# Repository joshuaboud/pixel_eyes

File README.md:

# pixel_eyes
WS2812S Pixel Eyes

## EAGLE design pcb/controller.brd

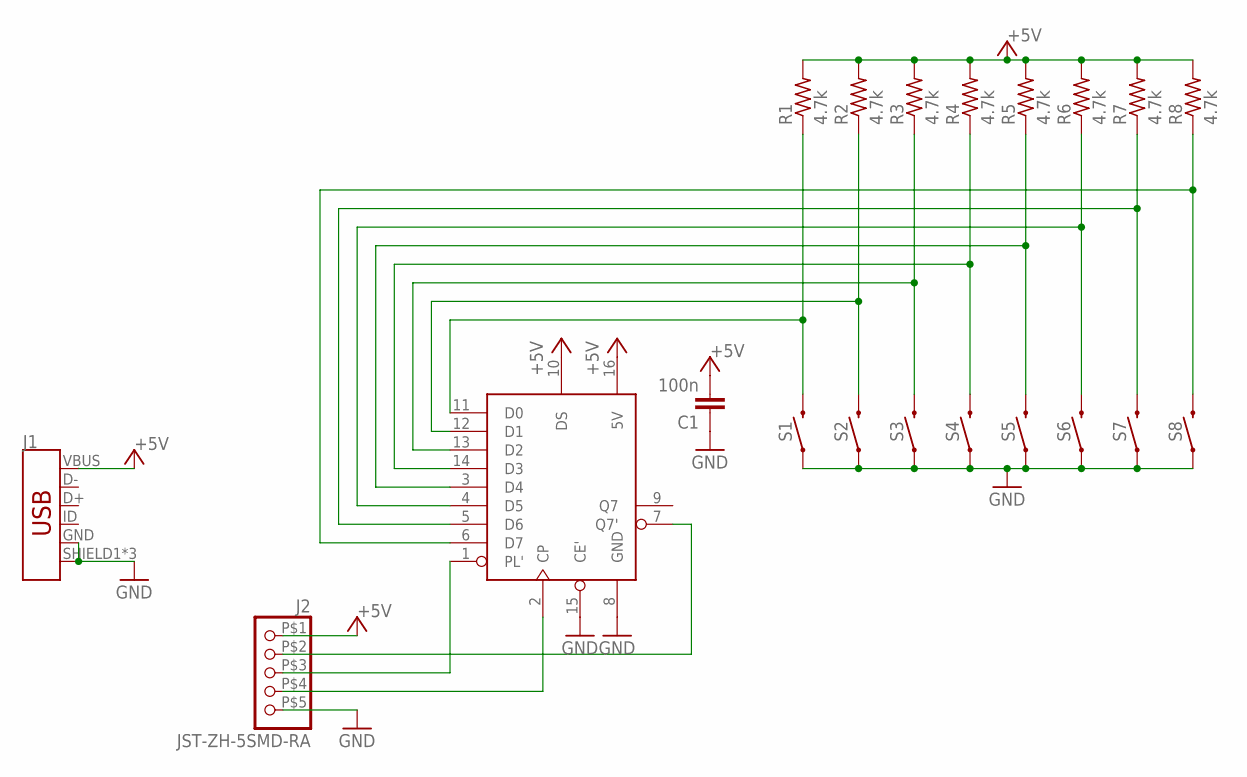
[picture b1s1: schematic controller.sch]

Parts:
C1: 100n; C0603
J1: USB_MICRO-B_FEMALE-SMT; USB-B-MICRO-SMD
J2: JST-ZH-5SMD-RA; JST-ZH-5-SMD-RA
R1, R2, R3, R4, R5, R6, R7, R8: 4.7k; R0603
S1, S2, S3, S4, S5, S6, S7, S8: MOMENTARY-SWITCH-SPST-SMD-6.0X3.5MM; TACTILE_SWITCH_SMD_6.0X3.5MM
U1: 74HCT165TSSOP16; SOP65P640X110-16N

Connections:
+5V: C1.2, J1.VBUS, J2.P$1 (1), R1.2, R2.2, R3.2, R4.2, R5.2, R6.2, R7.2, R8.2, U1.10 (DS), U1.16 (5V)
GND: C1.1, J1.GND, J1.SHIELD1 (SHIELD), J1.SHIELD2 (SHIELD), J1.SHIELD3 (SHIELD), J2.P$5 (5), S1.1, S2.1, S3.1, S4.1, S5.1, S6.1, S7.1, S8.1, U1.8 (GND), U1.15 (CE')
unnamed: J2.P$4 (4), U1.2 (CP)
unnamed: J2.P$3 (3), U1.1 (PL')
unnamed: J2.P$2 (2), U1.7 (Q7')
unnamed: R1.1, S1.2, U1.11 (D0)
unnamed: R2.1, S2.2, U1.12 (D1)
unnamed: R3.1, S3.2, U1.13 (D2)
unnamed: R4.1, S4.2, U1.14 (D3)
unnamed: R5.1, S5.2, U1.3 (D4)
unnamed: R6.1, S6.2, U1.4 (D5)
unnamed: R7.1, S7.2, U1.5 (D6)
unnamed: R8.1, S8.2, U1.6 (D7)

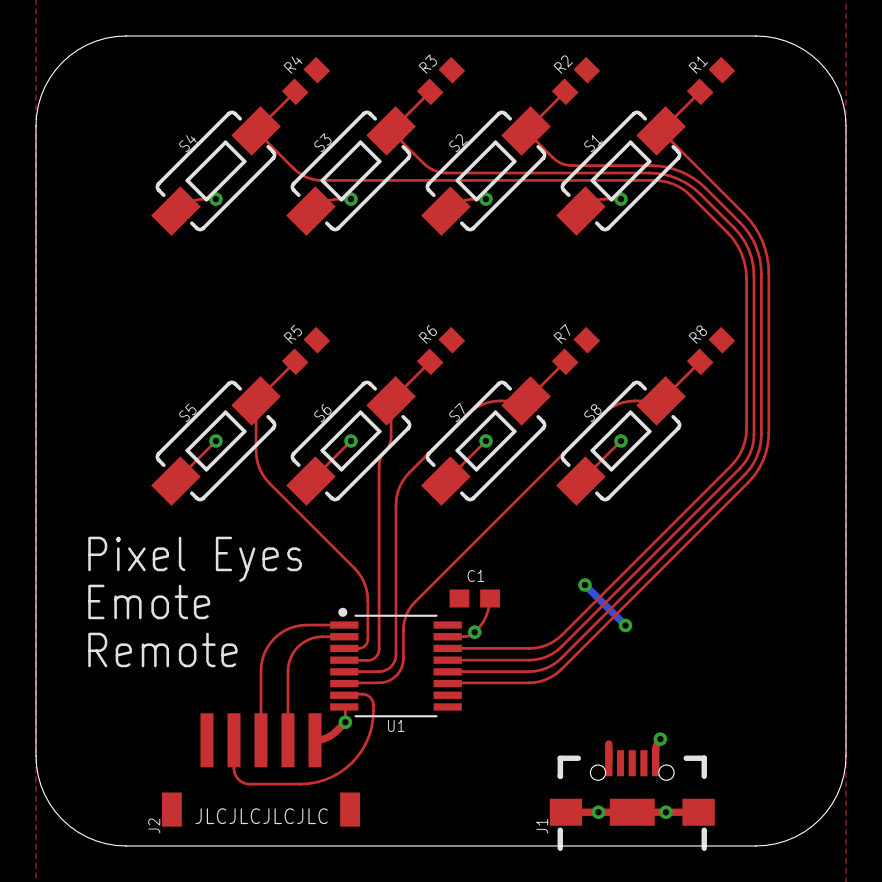
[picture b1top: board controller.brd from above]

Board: 2 copper layers, 45.0 x 45.0 mm, 22 parts (2 on the bottom side), 13 nets.

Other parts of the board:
U$1: SIGNATURE
U$3: LOGO_SILKSCREEN

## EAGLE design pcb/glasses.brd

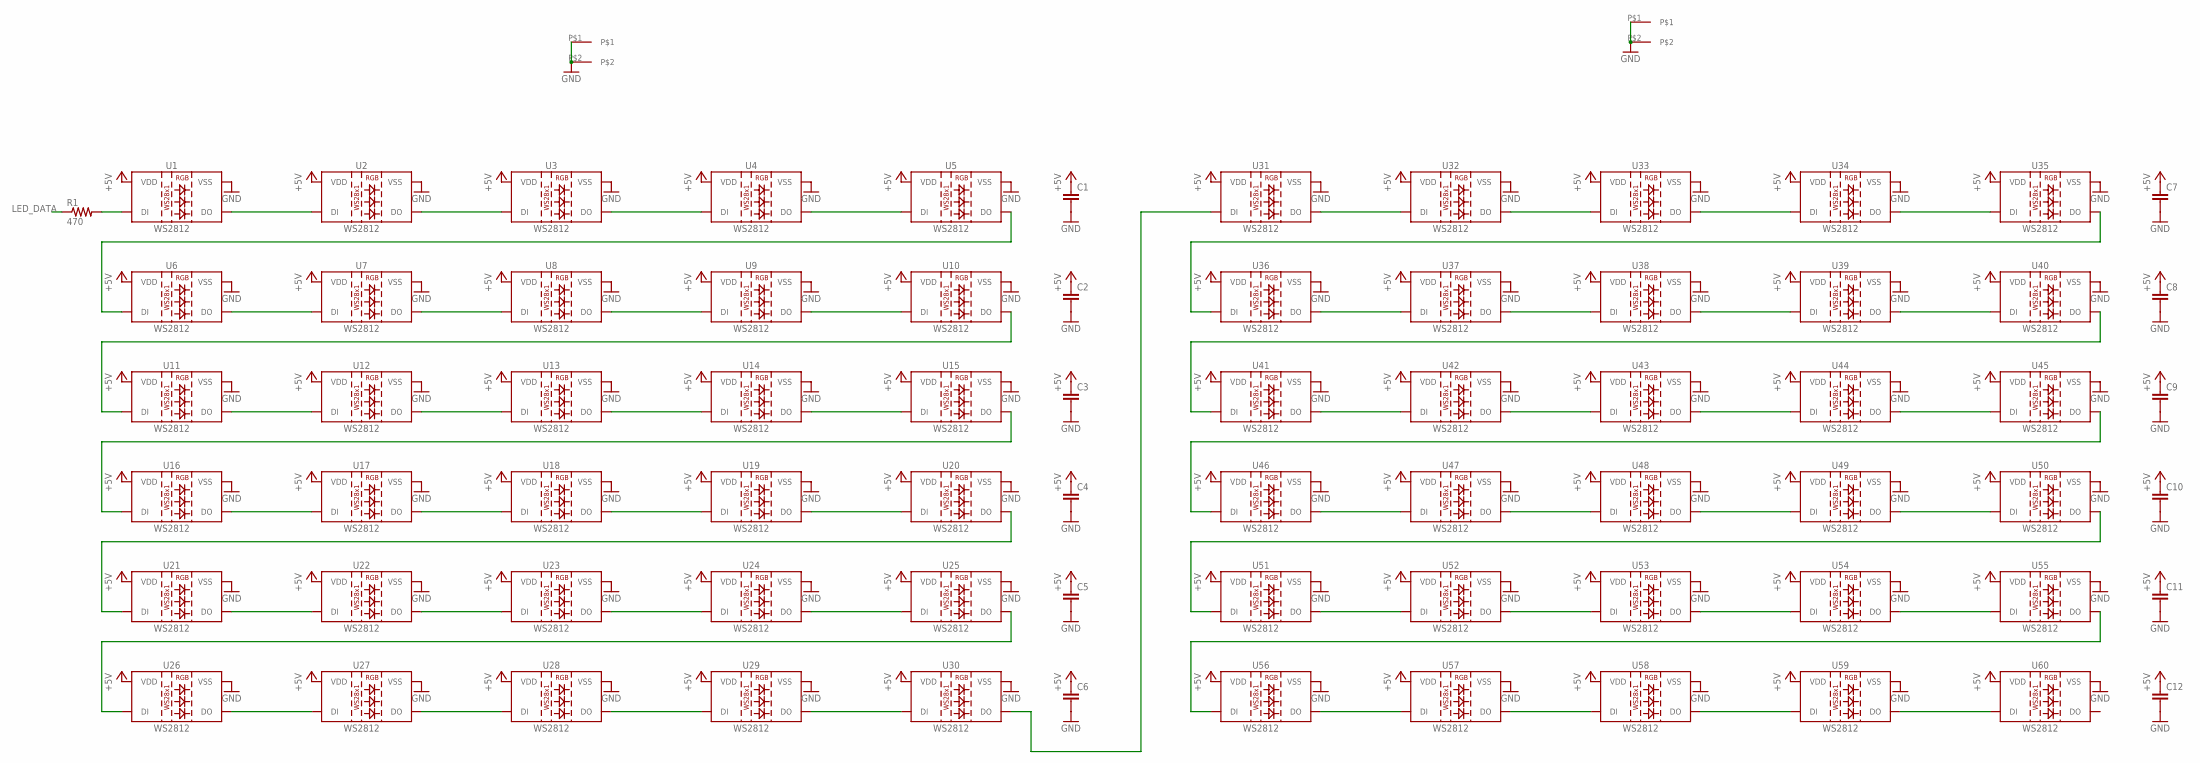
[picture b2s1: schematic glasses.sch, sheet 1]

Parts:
C1, C2, C3, C4, C5, C6, C7, C8, C9, C10, C11, C12: C-EUC0603; C0603
R1: 470; R0603
U1, U2, U3, U4, U5, U6, U7, U8, U9, U10, U11, U12, U13, U14, U15, U16, U17, U18, U19, U20, U21, U22, U23, U24, U25, U26, U27, U28, U29, U30, U31, U32, U33, U34, U35, U36, U37, U38, U39, U40, U41, U42, U43, U44, U45, U46, U47, U48, U49, U50, U51, U52, U53, U54, U55, U56, U57, U58, U59, U60: WS2812; LED-TRICOLOR-5050-IC
U$4, U$5: GLASSES_HINGE

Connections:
+5V: C1.1, C2.1, C3.1, C4.1, C5.1, C6.1, C7.1, C8.1, C9.1, C10.1, C11.1, C12.1, U1.3 (VDD), U1.5 (VDD), U2.3 (VDD), U2.5 (VDD), U3.3 (VDD), U3.5 (VDD), U4.3 (VDD), U4.5 (VDD), U5.3 (VDD), U5.5 (VDD), U6.3 (VDD), U6.5 (VDD), U7.3 (VDD), U7.5 (VDD), U8.3 (VDD), U8.5 (VDD), U9.3 (VDD), U9.5 (VDD), U10.3 (VDD), U10.5 (VDD), U11.3 (VDD), U11.5 (VDD), U12.3 (VDD), U12.5 (VDD), U13.3 (VDD), U13.5 (VDD), U14.3 (VDD), U14.5 (VDD), U15.3 (VDD), U15.5 (VDD), U16.3 (VDD), U16.5 (VDD), U17.3 (VDD), U17.5 (VDD), U18.3 (VDD), U18.5 (VDD), U19.3 (VDD), U19.5 (VDD), U20.3 (VDD), U20.5 (VDD), U21.3 (VDD), U21.5 (VDD), U22.3 (VDD), U22.5 (VDD), U23.3 (VDD), U23.5 (VDD), U24.3 (VDD), U24.5 (VDD), U25.3 (VDD), U25.5 (VDD), U26.3 (VDD), U26.5 (VDD), U27.3 (VDD), U27.5 (VDD), U28.3 (VDD), U28.5 (VDD), U29.3 (VDD), U29.5 (VDD), U30.3 (VDD), U30.5 (VDD), U31.3 (VDD), U31.5 (VDD), U32.3 (VDD), U32.5 (VDD), U33.3 (VDD), U33.5 (VDD), U34.3 (VDD), U34.5 (VDD), U35.3 (VDD), U35.5 (VDD), U36.3 (VDD), U36.5 (VDD), U37.3 (VDD), U37.5 (VDD), U38.3 (VDD), U38.5 (VDD), U39.3 (VDD), U39.5 (VDD), U40.3 (VDD), U40.5 (VDD), U41.3 (VDD), U41.5 (VDD), U42.3 (VDD), U42.5 (VDD), U43.3 (VDD), U43.5 (VDD), U44.3 (VDD), U44.5 (VDD), U45.3 (VDD), U45.5 (VDD), U46.3 (VDD), U46.5 (VDD), U47.3 (VDD), U47.5 (VDD), U48.3 (VDD), U48.5 (VDD), U49.3 (VDD), U49.5 (VDD), U50.3 (VDD), U50.5 (VDD), U51.3 (VDD), U51.5 (VDD), U52.3 (VDD), U52.5 (VDD), U53.3 (VDD), U53.5 (VDD), U54.3 (VDD), U54.5 (VDD), U55.3 (VDD), U55.5 (VDD), U56.3 (VDD), U56.5 (VDD), U57.3 (VDD), U57.5 (VDD), U58.3 (VDD), U58.5 (VDD), U59.3 (VDD), U59.5 (VDD), U60.3 (VDD), U60.5 (VDD); also elsewhere on the board
GND: C1.2, C2.2, C3.2, C4.2, C5.2, C6.2, C7.2, C8.2, C9.2, C10.2, C11.2, C12.2, U1.6 (VSS), U2.6 (VSS), U3.6 (VSS), U4.6 (VSS), U5.6 (VSS), U6.6 (VSS), U7.6 (VSS), U8.6 (VSS), U9.6 (VSS), U10.6 (VSS), U11.6 (VSS), U12.6 (VSS), U13.6 (VSS), U14.6 (VSS), U15.6 (VSS), U16.6 (VSS), U17.6 (VSS), U18.6 (VSS), U19.6 (VSS), U20.6 (VSS), U21.6 (VSS), U22.6 (VSS), U23.6 (VSS), U24.6 (VSS), U25.6 (VSS), U26.6 (VSS), U27.6 (VSS), U28.6 (VSS), U29.6 (VSS), U30.6 (VSS), U31.6 (VSS), U32.6 (VSS), U33.6 (VSS), U34.6 (VSS), U35.6 (VSS), U36.6 (VSS), U37.6 (VSS), U38.6 (VSS), U39.6 (VSS), U40.6 (VSS), U41.6 (VSS), U42.6 (VSS), U43.6 (VSS), U44.6 (VSS), U45.6 (VSS), U46.6 (VSS), U47.6 (VSS), U48.6 (VSS), U49.6 (VSS), U50.6 (VSS), U51.6 (VSS), U52.6 (VSS), U53.6 (VSS), U54.6 (VSS), U55.6 (VSS), U56.6 (VSS), U57.6 (VSS), U58.6 (VSS), U59.6 (VSS), U60.6 (VSS), U$4.P$1, U$4.P$2, U$5.P$1, U$5.P$2; also elsewhere on the board
LED_DATA: R1.1; also elsewhere on the board
unnamed: U1.1 (DO), U2.2 (DI)
unnamed: U2.1 (DO), U3.2 (DI)
unnamed: U3.1 (DO), U4.2 (DI)
unnamed: U4.1 (DO), U5.2 (DI)
unnamed: U5.1 (DO), U6.2 (DI)
unnamed: U6.1 (DO), U7.2 (DI)
unnamed: U7.1 (DO), U8.2 (DI)
unnamed: U8.1 (DO), U9.2 (DI)
unnamed: U9.1 (DO), U10.2 (DI)
unnamed: U10.1 (DO), U11.2 (DI)
unnamed: U11.1 (DO), U12.2 (DI)
unnamed: U12.1 (DO), U13.2 (DI)
unnamed: U13.1 (DO), U14.2 (DI)
unnamed: U14.1 (DO), U15.2 (DI)
unnamed: U15.1 (DO), U16.2 (DI)
unnamed: U16.1 (DO), U17.2 (DI)
unnamed: U17.1 (DO), U18.2 (DI)
unnamed: U18.1 (DO), U19.2 (DI)
unnamed: U19.1 (DO), U20.2 (DI)
unnamed: U20.1 (DO), U21.2 (DI)
unnamed: U21.1 (DO), U22.2 (DI)
unnamed: U22.1 (DO), U23.2 (DI)
unnamed: U23.1 (DO), U24.2 (DI)
unnamed: U24.1 (DO), U25.2 (DI)
unnamed: U25.1 (DO), U26.2 (DI)
unnamed: U26.1 (DO), U27.2 (DI)
unnamed: U27.1 (DO), U28.2 (DI)
unnamed: U28.1 (DO), U29.2 (DI)
unnamed: U29.1 (DO), U30.2 (DI)
unnamed: U31.1 (DO), U32.2 (DI)
unnamed: U32.1 (DO), U33.2 (DI)
unnamed: U33.1 (DO), U34.2 (DI)
unnamed: U34.1 (DO), U35.2 (DI)
unnamed: U35.1 (DO), U36.2 (DI)
unnamed: U36.1 (DO), U37.2 (DI)
unnamed: U37.1 (DO), U38.2 (DI)
unnamed: U38.1 (DO), U39.2 (DI)
unnamed: U39.1 (DO), U40.2 (DI)
unnamed: U40.1 (DO), U41.2 (DI)
unnamed: U41.1 (DO), U42.2 (DI)
unnamed: U42.1 (DO), U43.2 (DI)
unnamed: U43.1 (DO), U44.2 (DI)
unnamed: U44.1 (DO), U45.2 (DI)
unnamed: U45.1 (DO), U46.2 (DI)
unnamed: U46.1 (DO), U47.2 (DI)
unnamed: U47.1 (DO), U48.2 (DI)
unnamed: U48.1 (DO), U49.2 (DI)
unnamed: U49.1 (DO), U50.2 (DI)
unnamed: U50.1 (DO), U51.2 (DI)
unnamed: U51.1 (DO), U52.2 (DI)
unnamed: U52.1 (DO), U53.2 (DI)
unnamed: U53.1 (DO), U54.2 (DI)
unnamed: U54.1 (DO), U55.2 (DI)
unnamed: U55.1 (DO), U56.2 (DI)
unnamed: U56.1 (DO), U57.2 (DI)
unnamed: U57.1 (DO), U58.2 (DI)
unnamed: U58.1 (DO), U59.2 (DI)
unnamed: U59.1 (DO), U60.2 (DI)
unnamed: U30.1 (DO), U31.2 (DI)
unnamed: R1.2, U1.2 (DI)

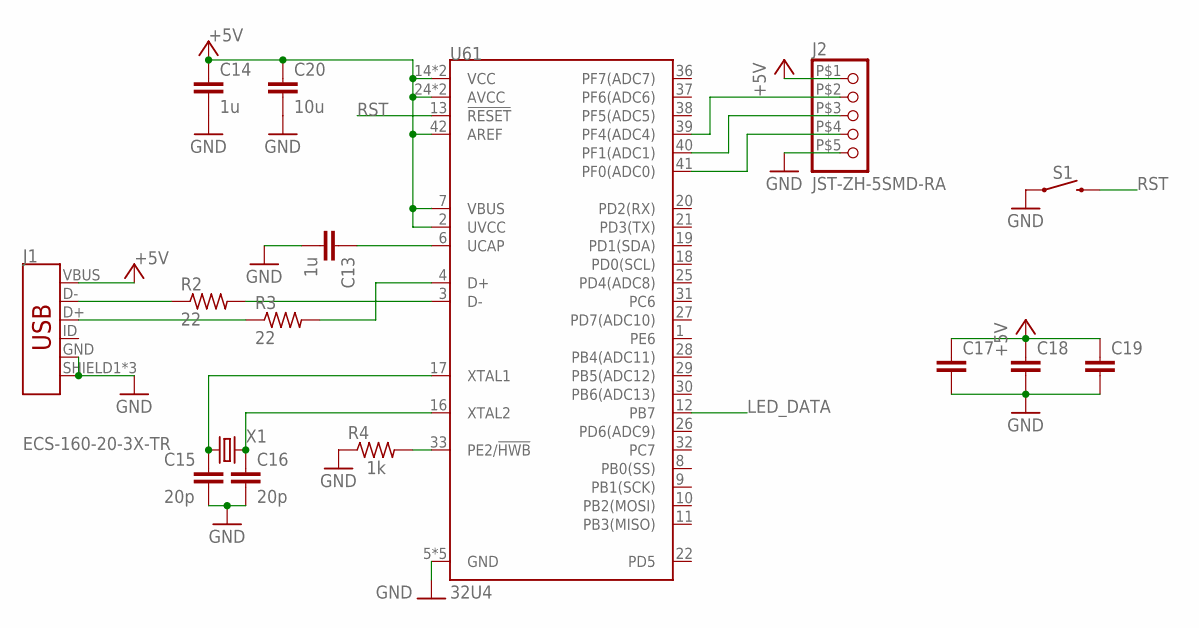
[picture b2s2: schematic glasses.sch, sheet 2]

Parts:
C13, C14: 1u; C0603
C15, C16: 20p; C0603
C17, C18, C19: C-EUC0603; C0603
C20: 10u; C0603
J1: USB_MICRO-B_FEMALE-SMT; USB-B-MICRO-SMD
J2: JST-ZH-5SMD-RA; JST-ZH-5-SMD-RA
R2, R3: 22; R0603
R4: 1k; R0603
S1: MOMENTARY-SWITCH-SPST-SMD-6.0X3.5MM; TACTILE_SWITCH_SMD_6.0X3.5MM
U61: 32U4; QFN-44
X1: ECS-160-20-3X-TR; CRYSTAL-SMD-5X3.2-2PAD

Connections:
+5V: C14.1, C17.1, C18.1, C19.1, C20.1, J1.VBUS, J2.P$1 (1), U61.2 (UVCC), U61.7 (VBUS), U61.14 (VCC), U61.24 (AVCC), U61.34 (VCC), U61.42 (AREF), U61.44 (AVCC); also elsewhere on the board
GND: C13.2, C14.2, C15.2, C16.2, C17.2, C18.2, C19.2, C20.2, J1.GND, J1.SHIELD1 (SHIELD), J1.SHIELD2 (SHIELD), J1.SHIELD3 (SHIELD), J2.P$5 (5), R4.1, S1.1, U61.5 (GND), U61.15 (GND), U61.23 (GND), U61.35 (GND), U61.43 (GND); also elsewhere on the board
LED_DATA: U61.12 (PB7); also elsewhere on the board
unnamed: J2.P$4 (4), U61.41 (PF0(ADC0))
unnamed: C13.1, U61.6 (UCAP)
unnamed: J2.P$3 (3), U61.40 (PF1(ADC1))
unnamed: J2.P$2 (2), U61.39 (PF4(ADC4))
unnamed: C16.1, U61.16 (XTAL2), X1.P$2 (2)
unnamed: C15.1, U61.17 (XTAL1), X1.P$1 (1)
unnamed: R4.2, U61.33 (PE2/!HWB)
RST: S1.2, U61.13 (!RESET)
USB1_N: J1.D-, R2.1
USB1_P: J1.D+, R3.1
USB_N: R2.2, U61.3 (D-)
USB_P: R3.2, U61.4 (D+)

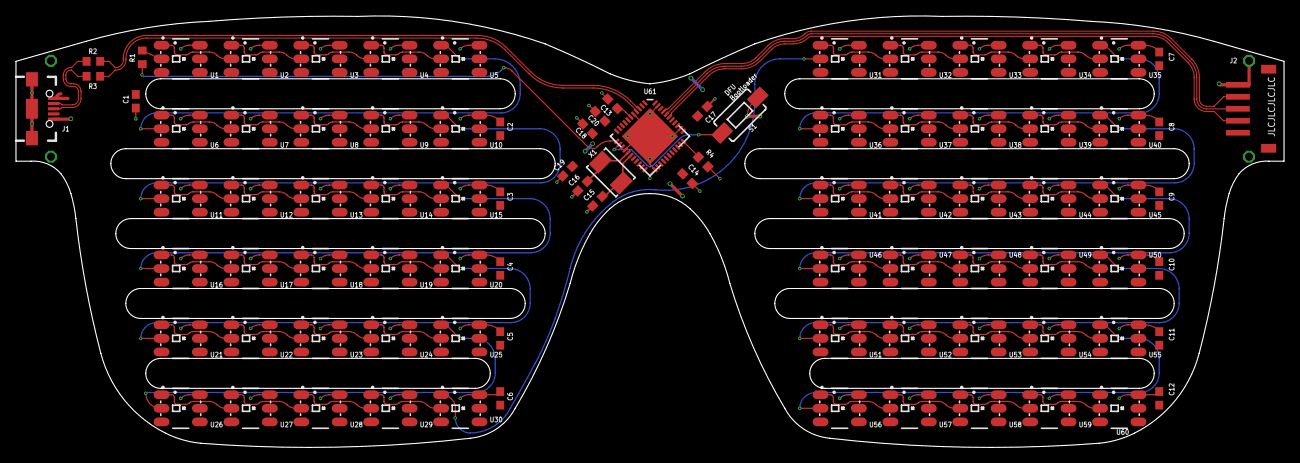
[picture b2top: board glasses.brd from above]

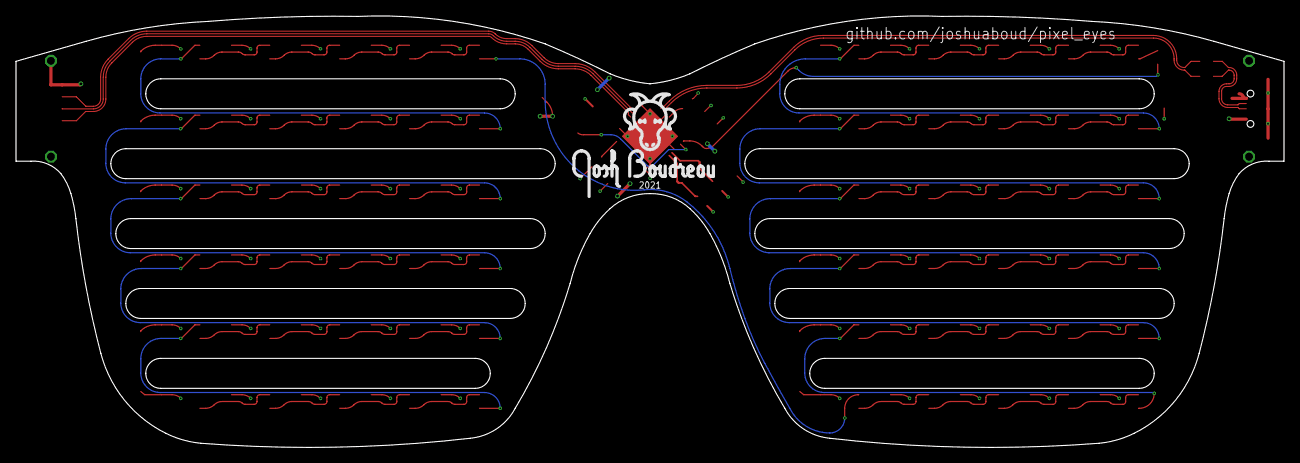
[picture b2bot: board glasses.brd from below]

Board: 2 copper layers, 158.8 x 54.0 mm, 93 parts (2 on the bottom side), 75 nets.

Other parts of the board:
U$1: SIGNATURE
U$2: LOGO_SILKSCREEN

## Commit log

2021-08-13 start route data lines
2021-08-13 finish wiring
2021-08-13 change connector to TE AMP 171826-3
2021-08-13 add library
2021-08-16 start controller design
2021-08-16 change to non-arduino atmega32u4
2021-08-16 start source
2021-08-17 ignore ccls cache
2021-08-17 add License.txt for WS2812 lib
2021-08-17 add build and dist
2021-08-17 ignore vscode settings
2021-08-17 set up makefile
2021-08-17 finish makefile
2021-08-17 change from c11 to gnu11 standard
2021-08-17 work on source
2021-08-18 create Frame struct
2021-08-18 add emote lut
2021-08-19 add simulation
2021-08-19 change RGB6 to be union of bf and uint8_t
2021-08-19 bug fixes
2021-08-19 remove LED number output
2021-08-19 finish simulation env
2021-08-20 add program to draw emotes
2021-08-20 implement saving frames to .c file
2021-08-24 implement saving, loading, frame insert/delete
2021-08-24 add changing duration
2021-08-24 append frame to end
2021-08-24 add edit frames target
2021-08-24 add default blink animation
2021-08-30 add previewing frames
2021-08-30 save frames
2021-09-05 make full glasses and add mcu to them
2021-09-06 finish up glasses
2021-09-06 finish controller
2021-09-06 update resistor values
2021-09-06 update values and name placement
2021-09-06 start bill of materials
2021-09-06 add connector devices
2021-09-06 touch up silkscreen and traces
2021-09-06 add more parts
2021-09-06 ignore libreoffice lock files
2021-09-06 finish BOM, TODO: digi-key pn's
2021-09-06 not sure what changed
2021-09-06 add avr-isp header to glasses
2021-09-06 order from LCSC instead
2021-09-06 optimize some routing
2021-09-06 add restrict under MCU
2021-09-06 connect MCU grounds under EP
2021-09-06 fix X1 silkscreen and caps
2021-09-06 add reset switch to count
2021-09-06 fix font
2021-09-07 add 10uF VBUS cap
2021-09-07 fix paste on mcu
2021-09-07 rename eye.{brd,sch} to glasses.{brd,sch}
2021-09-07 add gerber files
2021-09-07 place JLC number under connector and add year
2021-09-07 update silkscreen
2021-09-07 ran DRC and moved vias
2021-09-07 update BOM
2021-09-07 ran DRC
2021-09-07 add step file for glasses PCB to model arms
2021-09-07 make all eye frames copy
2021-09-07 change clock speed to 1MHz, use dfu-programmer
2021-09-30 force erase and add reset run target
2021-09-30 update input port
2021-09-30 update output pin
2021-09-30 add test
2021-10-01 lower brightness
2021-10-01 fix ldflags and use 8MHz F_CPU
2021-10-01 include config
2021-10-01 increase reset time
2021-10-01 scale clock to DIV2 (8MHz)
2021-10-07 show and allow changing last_frame
2021-10-07 improve eye animation
2021-10-07 finish default eye animation
2021-10-07 change to 8 emotes
2021-10-07 add numbers to other emotes
2021-10-07 better eye animation
2021-10-07 try to get shift reg working
2021-10-07 rename state_machine to loop, enable input pullup
2021-10-07 remove ninth frame
2021-10-07 add headers and comments to files
2021-10-07 fix typo
2021-10-07 disable JTAG to use PORTF and speed up shifting
2021-10-07 start wink
2021-10-07 add wink
2021-10-07 reset duration counter when changing emote
2021-10-07 increase brightness
2021-10-07 add anger
2021-10-07 speed up shift
2021-10-07 add cry
2021-10-07 finish all animations
2021-10-07 allow brightness to be adjusted in runtime
2021-10-08 add glasses arms STLs
2021-10-08 finalise arms

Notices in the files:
parts and their libraries:
SparkFun-Connectors: Licensing: Creative Commons ShareAlike 4.0 International - https://creativecommons.org/licenses/by-sa/4.0
